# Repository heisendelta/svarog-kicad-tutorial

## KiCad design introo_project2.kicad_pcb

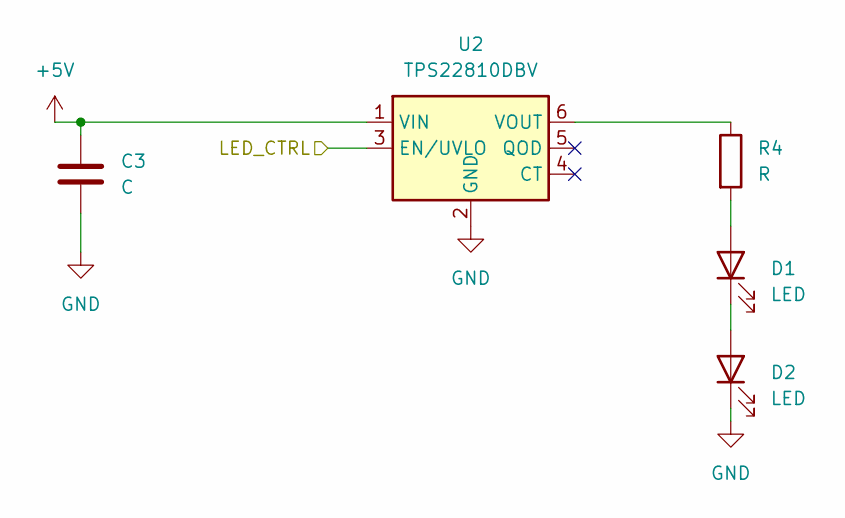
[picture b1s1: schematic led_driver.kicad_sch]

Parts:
C3: C; C_0603_1608Metric
D1, D2: LED; LED_Cree-XHP50_3V_HighDensity
R4: R; R_0603_1608Metric
U2: TPS22810DBV; SOT-23-6

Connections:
+5V: C3.1, U2.1 (VIN); also elsewhere on the board
/LED_Driver/LED_CTRL: U2.3 (EN/UVLO); also elsewhere on the board
GND: C3.2, D2.1 (K), U2.2 (GND); also elsewhere on the board
unnamed: D1.2 (A), R4.2
unnamed: D1.1 (K), D2.2 (A)
unnamed: R4.1, U2.6 (VOUT)

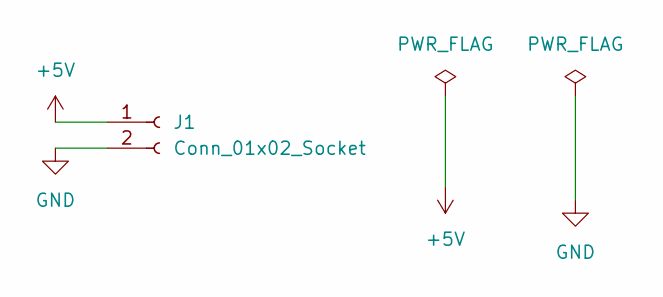
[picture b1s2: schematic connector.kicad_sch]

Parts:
J1: Conn_01x02_Socket; Molex_Nano-Fit_105309-xx02_1x02_P2.50mm_Vertical

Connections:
+5V: J1.1; also elsewhere on the board
GND: J1.2; also elsewhere on the board

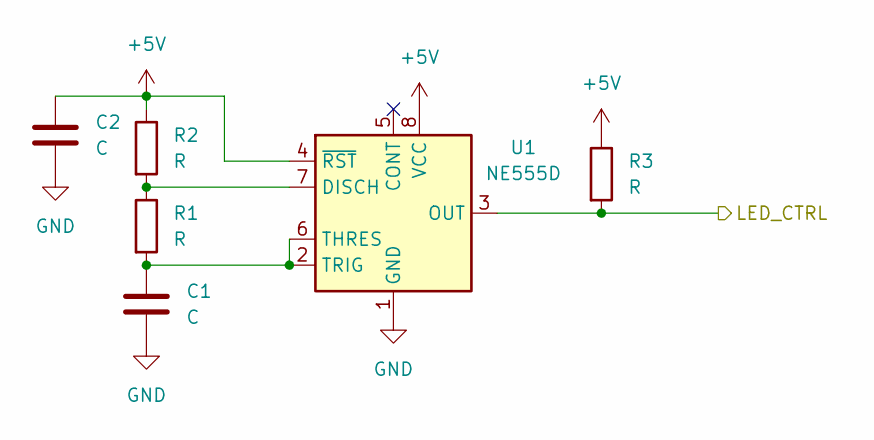
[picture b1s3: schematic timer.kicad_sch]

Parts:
C1, C2: C; C_0603_1608Metric
R1, R2, R3: R; R_0603_1608Metric
U1: NE555D; SOIC-8_3.9x4.9mm_P1.27mm

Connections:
+5V: C2.1, R2.1, R3.1, U1.4 (~RST), U1.8 (VCC); also elsewhere on the board
/LED_Driver/LED_CTRL: R3.2, U1.3 (OUT); also elsewhere on the board
GND: C1.2, C2.2, U1.1 (GND); also elsewhere on the board
unnamed: R1.1, R2.2, U1.7 (DISCH)
unnamed: C1.1, R1.2, U1.2 (TRIG), U1.6 (THRES)

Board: 2 copper layers, 12 parts (0 on the bottom side), 8 nets, no tracks yet.
